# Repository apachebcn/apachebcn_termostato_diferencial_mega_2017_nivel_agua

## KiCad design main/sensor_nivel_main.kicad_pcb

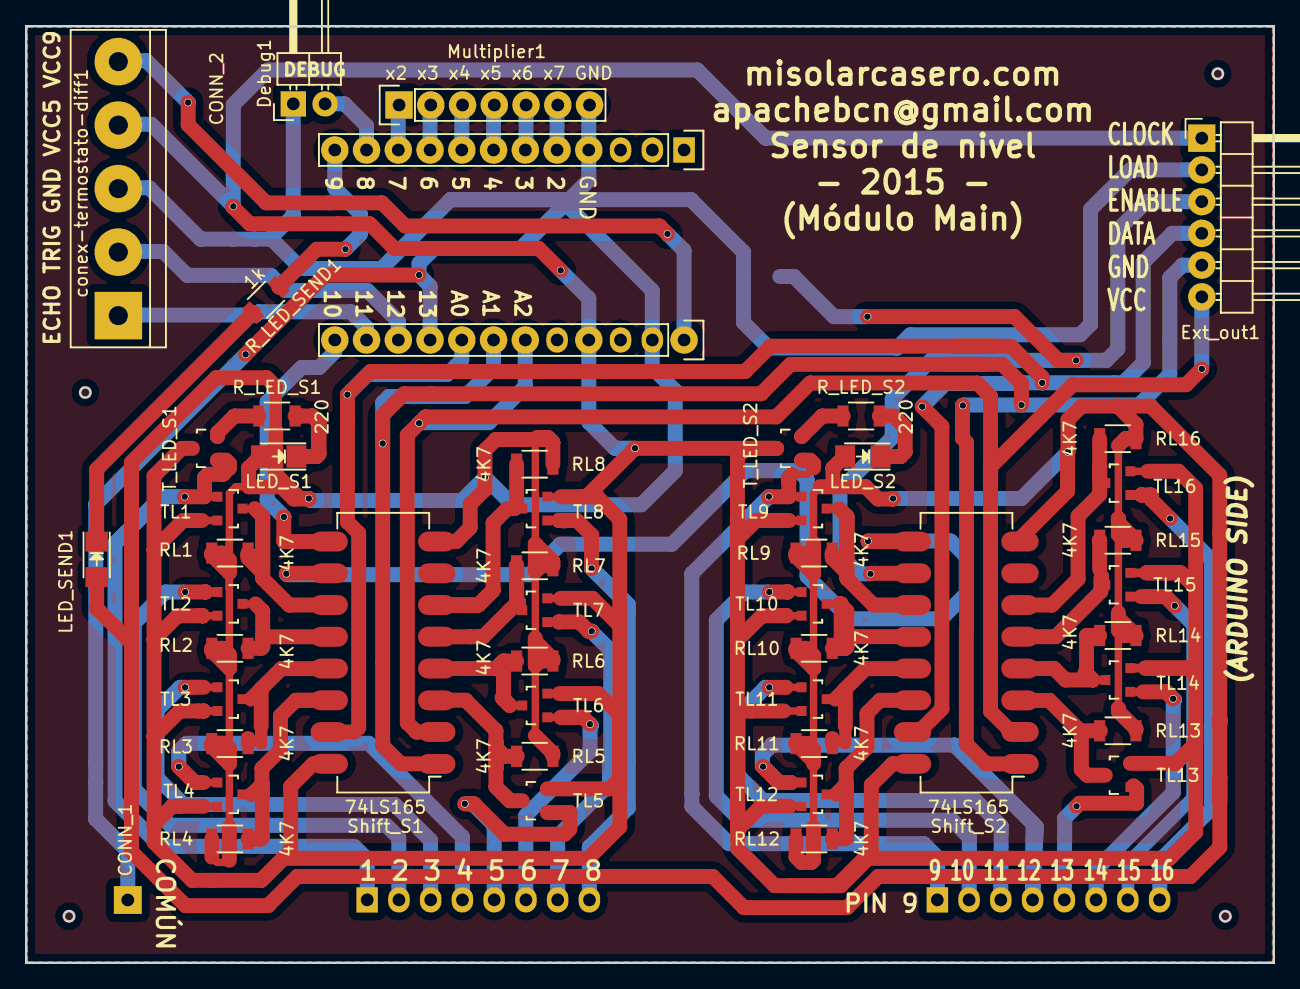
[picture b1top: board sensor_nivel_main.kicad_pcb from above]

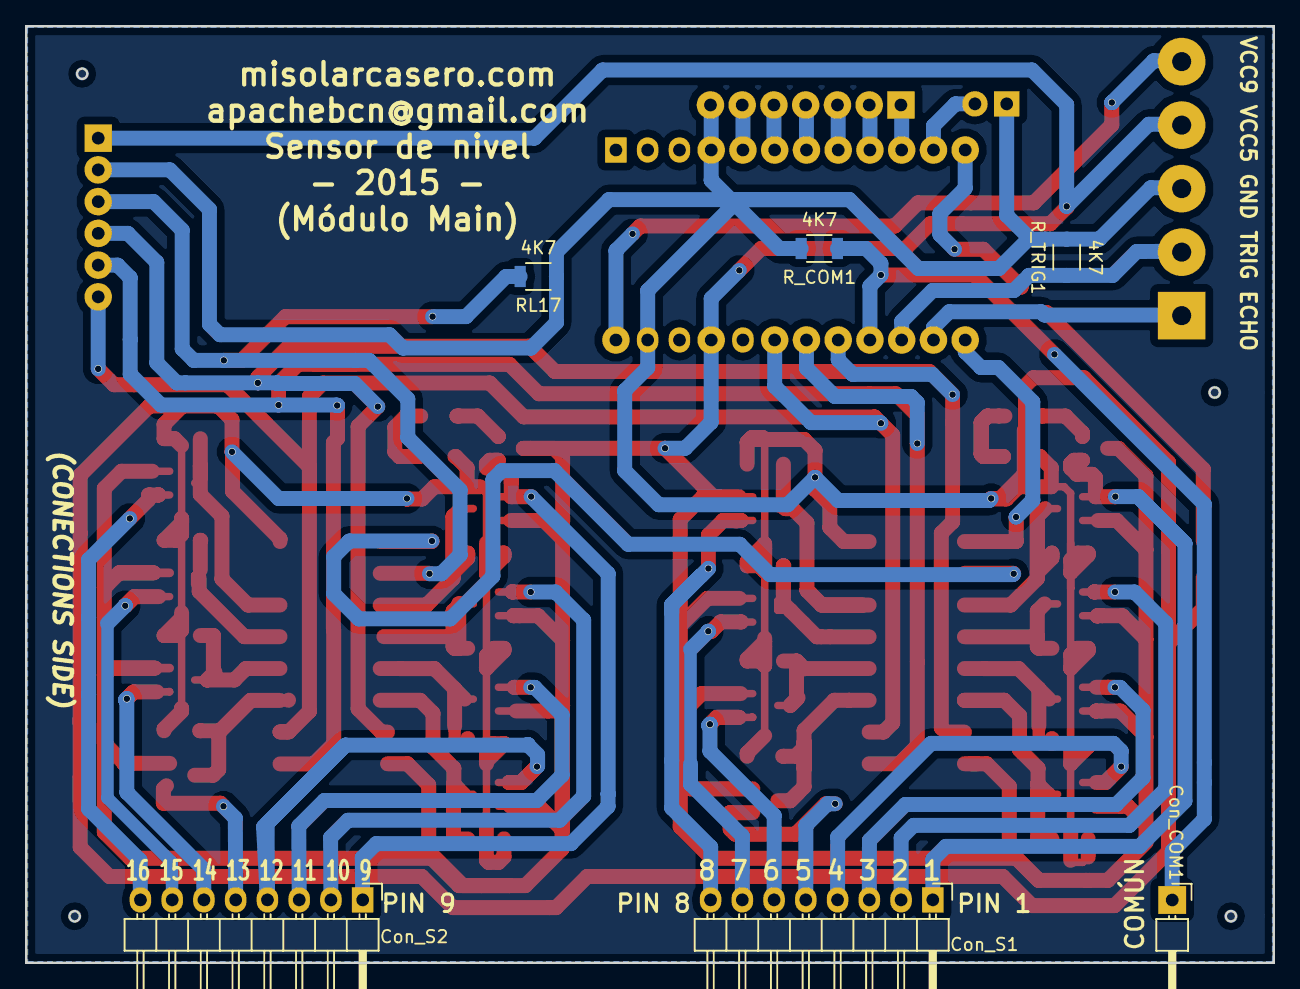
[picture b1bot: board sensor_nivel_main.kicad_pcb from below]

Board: 2 copper layers, 99.8 x 74.9 mm, 54 parts (6 on the bottom side), 57 nets.

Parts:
ARDUINO_L1: ARDUINO L; Pin_Header_Straight_1x12
ARDUINO_R1: ARDUINO_R; Pin_Header_Straight_1x12
Con_COM1: CONN_1; Pin_Header_Angled_1x01
Con_S1: CONN_1; Pin_Header_Angled_1x08
Con_S2: CONN_2; Pin_Header_Angled_1x08
Debug1: CONN_2; Pin_Header_Angled_1x02
Ext_out1: Vcc Gnd Data Enable Load Clock; Pin_Header_Angled_1x06
LED_S1, LED_S2: LED; LED-1206
LED_SEND1: LED; LED-1206
Multiplier1: x2 x3 x4 x5 x6 x7 GND; Pin_Header_Straight_1x07
RL1, RL2, RL3, RL4, RL5, RL6, RL7, RL8, RL9, RL10, RL11, RL12, RL13, RL14, RL15, RL16, RL17: 4K7; R_1206
R_COM1: 4K7; R_1206
R_LED_S1, R_LED_S2: 220; R_1206
R_LED_SEND1: 1k; R_1206
R_TRIG1: 4K7; R_1206
Shift_S1, Shift_S2: 74LS165; DIP-16_W7.62mm
TL1, TL2, TL3, TL4, TL5, TL6, TL7, TL8, TL9, TL10, TL11, TL12, TL13, TL14, TL15, TL16: BC849; SOT-23
T_LED_S1: BC337; SOT-23
T_LED_S2: BC849; SOT-23
conex-termostato-diff1: +9 +5 GND TRIG ECHO; bornier5

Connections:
2: ARDUINO_L1.5, Multiplier1.6
3: ARDUINO_L1.6, Multiplier1.5
4: ARDUINO_L1.7, Multiplier1.4
5: ARDUINO_L1.8, Multiplier1.3
6: ARDUINO_L1.9, Multiplier1.2
7: ARDUINO_L1.10, Multiplier1.1
8: ARDUINO_L1.11, Debug1.2
9: ARDUINO_L1.12, R_LED_SEND1.1
10: ARDUINO_R1.12, Shift_S1.9
11: ARDUINO_R1.11, conex-termostato-diff1.1
12: ARDUINO_R1.10, R_TRIG1.1, conex-termostato-diff1.2
13: ARDUINO_R1.9, Con_COM1.1, R_COM1.1
/L1: Con_S1.1, TL1.1, T_LED_S1.1
/L2: Con_S1.2, TL2.1
/L3: Con_S1.3, TL3.1
/L4: Con_S1.4, TL4.1
/L5: Con_S1.5, TL5.1
/L6: Con_S1.6, TL6.1
/L7: Con_S1.7, TL7.1
/L8: RL8.1, Shift_S1.6, TL8.3
/L9: Con_S2.1, TL9.1, T_LED_S2.1
/L10: Con_S2.2, TL10.1
/L11: Con_S2.3, TL11.1
/L12: Con_S2.4, TL12.1
/L13: Con_S2.5, TL13.1
/L14: Con_S2.6, TL14.1
/L15: Con_S2.7, TL15.1
/L16: RL16.1, Shift_S2.6, TL16.3
/S1_L1: RL1.2, Shift_S1.11, TL1.3
/S1_L2: RL2.2, Shift_S1.12, TL2.3
/S1_L3: RL3.2, Shift_S1.13, TL3.3
/S1_L4: RL4.2, Shift_S1.14, TL4.3
/S1_L5: RL5.1, Shift_S1.3, TL5.3
/S1_L6: RL6.1, Shift_S1.4, TL6.3
/S1_L7: RL7.1, Shift_S1.5, TL7.3
/S2_L5: RL13.1, Shift_S2.3, TL13.3
/S2_L6: RL14.1, Shift_S2.4, TL14.3
/S2_L7: RL15.1, Shift_S2.5, TL15.3
A0: ARDUINO_R1.8, Ext_out1.4, Shift_S1.15, Shift_S2.15
A1: ARDUINO_R1.7, Ext_out1.5, Shift_S1.1, Shift_S2.1
A2: ARDUINO_R1.6, Ext_out1.6, Shift_S1.2, Shift_S2.2
GND: ARDUINO_L1.4, ARDUINO_R1.2, Debug1.1, Ext_out1.2, LED_S1.2, LED_S2.2, LED_SEND1.2, Multiplier1.7, RL1.1, RL2.1, RL3.1, RL4.1, RL5.2, RL6.2, RL7.2, RL8.2, RL9.1, RL10.1, RL11.1, RL12.1, RL13.2, RL14.2, RL15.2, RL16.2, RL17.1, R_COM1.2, R_TRIG1.2, Shift_S1.8, Shift_S2.8, conex-termostato-diff1.3
unnamed: Con_S1.8, TL8.1
unnamed: Con_S2.8, TL16.1
unnamed: Ext_out1.3, RL17.2, Shift_S2.10
unnamed: LED_S1.1, R_LED_S1.2
unnamed: LED_S2.1, R_LED_S2.2
unnamed: LED_SEND1.1, R_LED_SEND1.2
unnamed: RL9.2, Shift_S2.11, TL9.3
unnamed: RL10.2, Shift_S2.12, TL10.3
unnamed: RL11.2, Shift_S2.13, TL11.3
unnamed: RL12.2, Shift_S2.14, TL12.3
unnamed: R_LED_S1.1, T_LED_S1.2
unnamed: R_LED_S2.1, T_LED_S2.2
unnamed: Shift_S1.10, Shift_S2.9
RAW: ARDUINO_R1.1, conex-termostato-diff1.5
VCC: ARDUINO_R1.4, Ext_out1.1, Shift_S1.16, Shift_S2.16, TL1.2, TL2.2, TL3.2, TL4.2, TL5.2, TL6.2, TL7.2, TL8.2, TL9.2, TL10.2, TL11.2, TL12.2, TL13.2, TL14.2, TL15.2, TL16.2, T_LED_S1.3, T_LED_S2.3, conex-termostato-diff1.4
